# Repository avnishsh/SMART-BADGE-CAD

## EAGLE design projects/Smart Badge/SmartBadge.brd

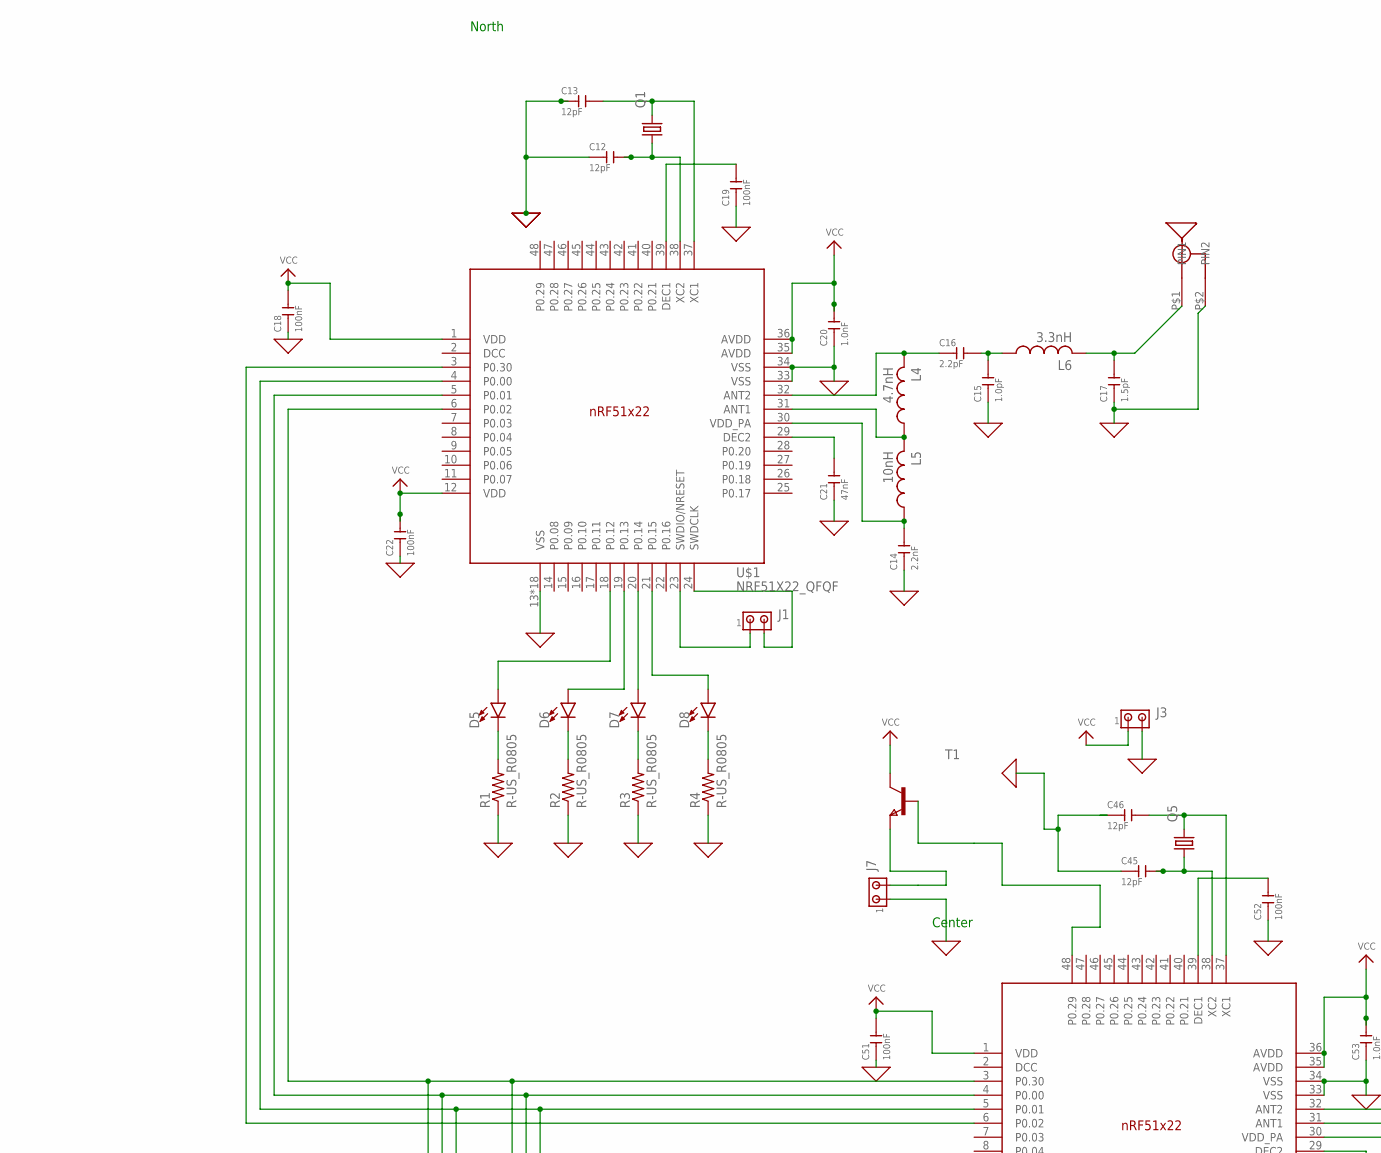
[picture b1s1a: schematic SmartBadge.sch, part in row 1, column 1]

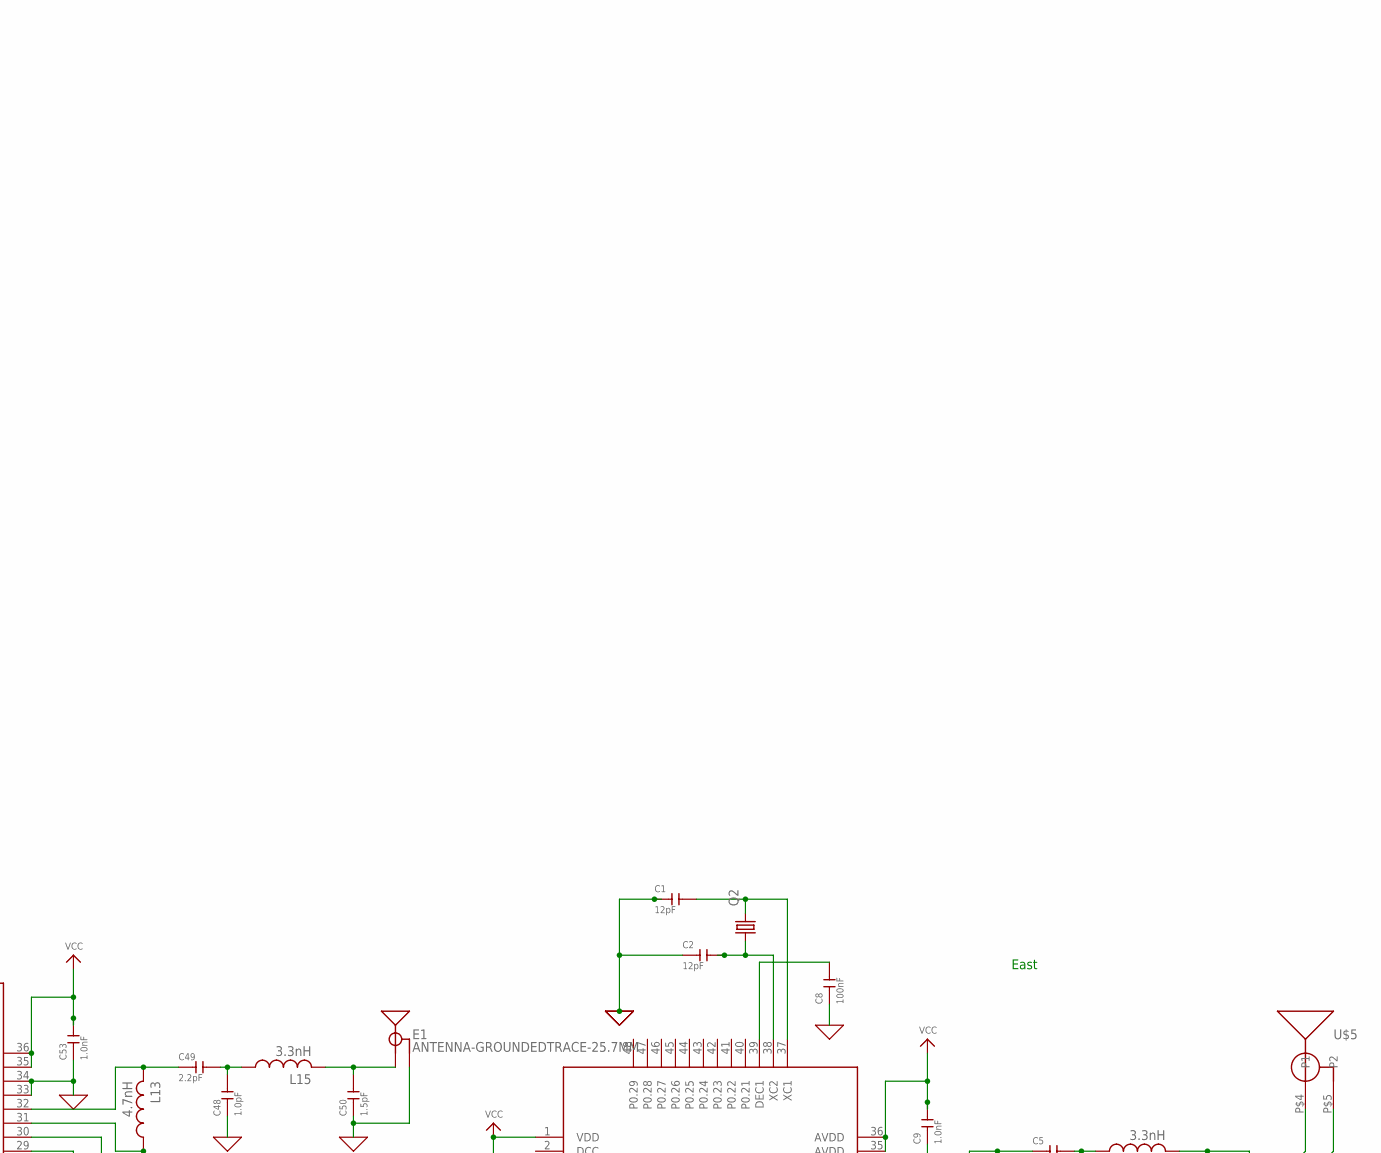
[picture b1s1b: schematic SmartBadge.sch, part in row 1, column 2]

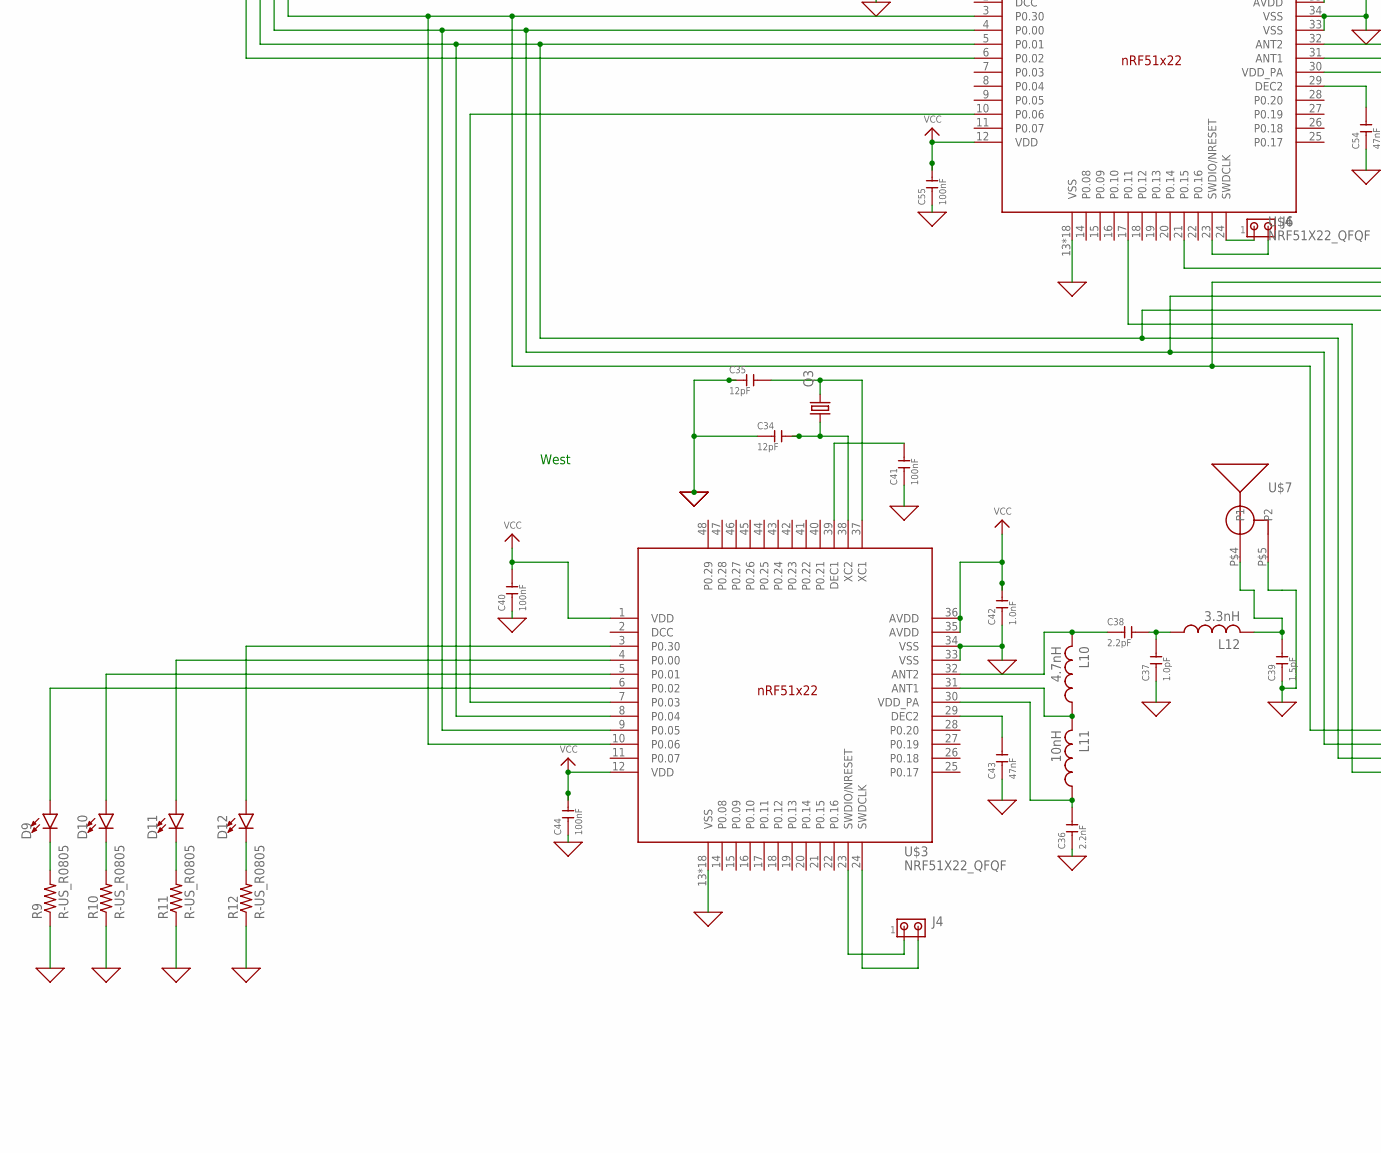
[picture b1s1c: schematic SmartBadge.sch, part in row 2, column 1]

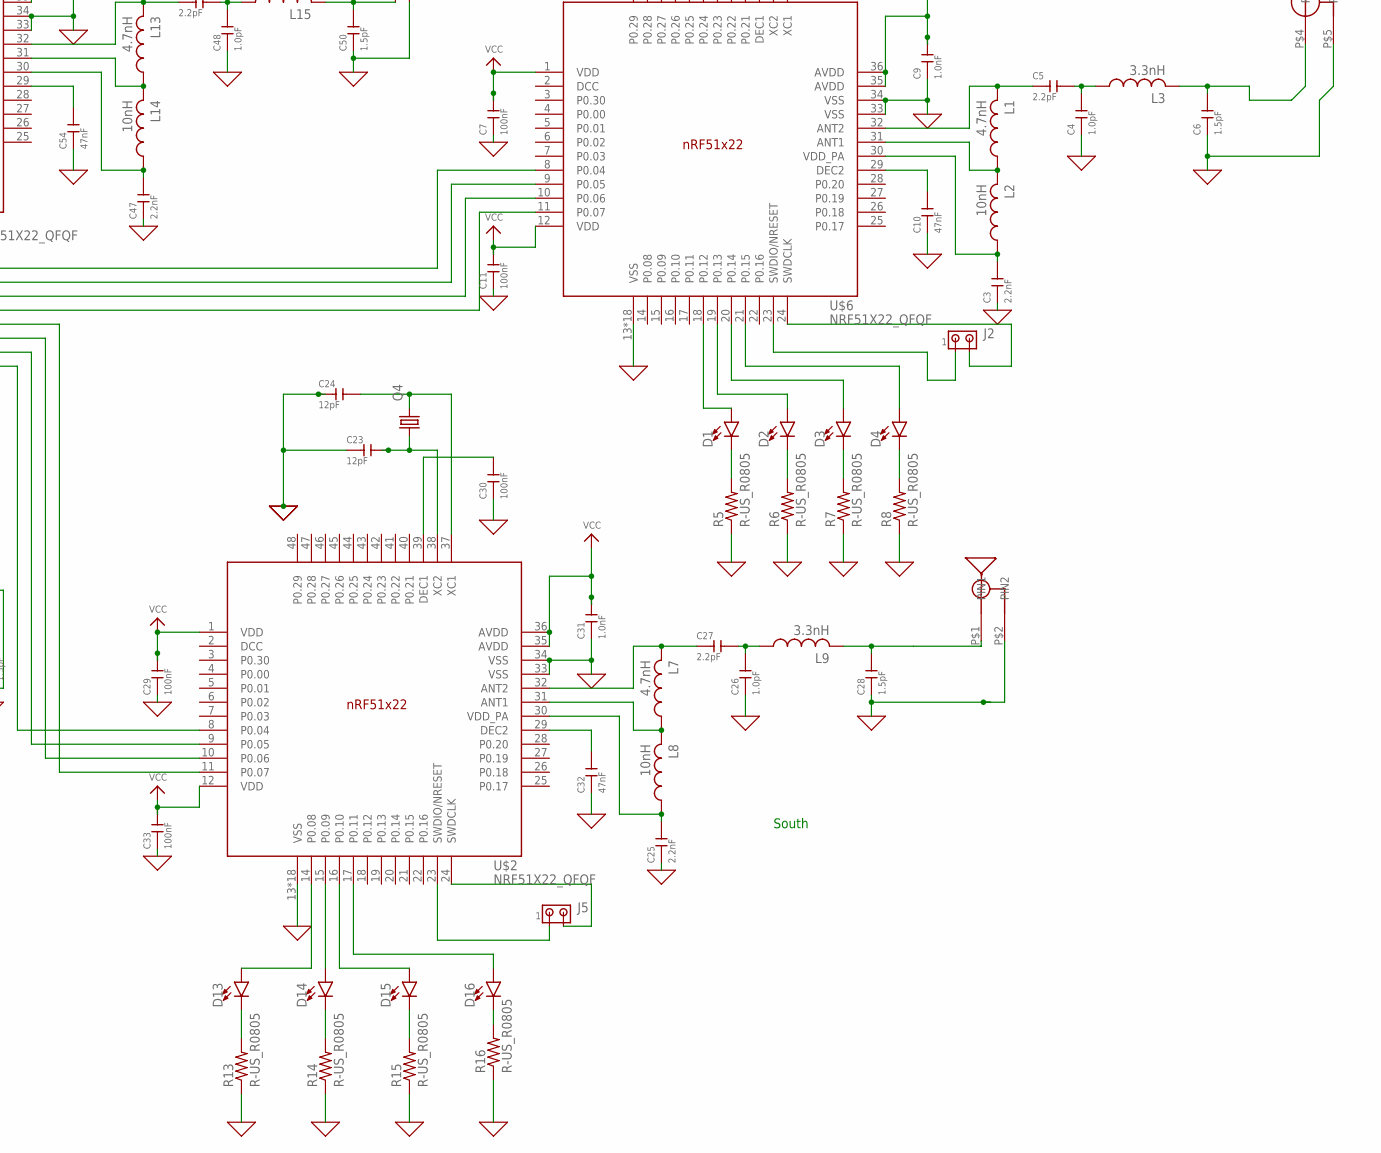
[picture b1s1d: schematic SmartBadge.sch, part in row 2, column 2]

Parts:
C1, C2, C12, C13, C23, C24, C34, C35, C45, C46: 12pF; C0805
C3, C14, C25, C36, C47: 2.2nF; C0805
C4, C15, C26, C37, C48: 1.0pF; C0805
C5, C16, C27, C38, C49: 2.2pF; C0805
C6, C17, C28, C39, C50: 1.5pF; C0805
C7, C8, C11, C18, C19, C22, C29, C30, C33, C40, C41, C44, C51, C52, C55: 100nF; C0805
C9, C20, C31, C42, C53: 1.0nF; C0805
C10, C21, C32, C43, C54: 47nF; C0805
D1, D2, D3, D4, D5, D6, D7, D8, D9, D10, D11, D12, D13, D14, D15, D16: LED-GREEN0603; LED-0603
E1: ANTENNA-GROUNDEDTRACE-25.7MM; TRACE_ANTENNA_2.4GHZ_25.7MM
J1, J2, J3, J4, J5, J6, J7: MTA02-100; 10X02MTA
L1, L4, L7, L10, L13: 4.7nH; RESC0805_L
L2, L5, L8, L11, L14: 10nH; RESC0805_L
L3, L6, L9, L12, L15: 3.3nH; RESC0805_L
Q1, Q2, Q3, Q4, Q5: KX-6; 2.5X2.0_KX-6
R1, R2, R3, R4, R5, R6, R7, R8, R9, R10, R11, R12, R13, R14, R15, R16: R-US_R0805; R0805
T1: NPNSOT323; SOT323
U$1, U$2, U$3, U$4, U$6: NRF51X22_QFQF; QFN40P600X600X90-48_N
U$5, U$7: YAGI_UDA; YAGIUDA
U$8, U$9: 2.4G_PATCH; PATCH

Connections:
0: C1.1, C2.1, C3.1, C4.1, C6.1, C7.1, C8.1, C9.1, C10.1, C11.1, C12.1, C13.1, C14.1, C15.1, C17.1, C18.1, C19.1, C20.1, C21.1, C22.1, C23.1, C24.1, C25.1, C26.1, C28.1, C29.1, C30.1, C31.1, C32.1, C33.1, C34.1, C35.1, C36.1, C37.1, C39.1, C40.1, C41.1, C42.1, C43.1, C44.1, C45.1, C46.1, C47.1, C48.1, C50.1, C51.1, C52.1, C53.1, C54.1, C55.1, E1.GND, E1.GND2 (GND), J3.2, J7.1, R1.1, R2.1, R3.1, R4.1, R5.1, R6.1, R7.1, R8.1, R9.1, R10.1, R11.1, R12.1, R13.1, R14.1, R15.1, R16.1, U$1.13 (VSS), U$1.33 (VSS), U$1.34 (VSS), U$1.PAD (VSS), U$1.PAD@VIA01 (VSS), U$1.PAD@VIA02 (VSS), U$1.PAD@VIA03 (VSS), U$1.PAD@VIA04 (VSS), U$1.PAD@VIA05 (VSS), U$1.PAD@VIA06 (VSS), U$1.PAD@VIA07 (VSS), U$1.PAD@VIA08 (VSS), U$1.PAD@VIA09 (VSS), U$1.PAD@VIA10 (VSS), U$1.PAD@VIA11 (VSS), U$1.PAD@VIA12 (VSS), U$1.PAD@VIA13 (VSS), U$1.PAD@VIA14 (VSS), U$1.PAD@VIA15 (VSS), U$1.PAD@VIA16 (VSS), U$2.13 (VSS), U$2.33 (VSS), U$2.34 (VSS), U$2.PAD (VSS), U$2.PAD@VIA01 (VSS), U$2.PAD@VIA02 (VSS), U$2.PAD@VIA03 (VSS), U$2.PAD@VIA04 (VSS), U$2.PAD@VIA05 (VSS), U$2.PAD@VIA06 (VSS), U$2.PAD@VIA07 (VSS), U$2.PAD@VIA08 (VSS), U$2.PAD@VIA09 (VSS), U$2.PAD@VIA10 (VSS), U$2.PAD@VIA11 (VSS), U$2.PAD@VIA12 (VSS), U$2.PAD@VIA13 (VSS), U$2.PAD@VIA14 (VSS), U$2.PAD@VIA15 (VSS), U$2.PAD@VIA16 (VSS), U$3.13 (VSS), U$3.33 (VSS), U$3.34 (VSS), U$3.PAD (VSS), U$3.PAD@VIA01 (VSS), U$3.PAD@VIA02 (VSS), U$3.PAD@VIA03 (VSS), U$3.PAD@VIA04 (VSS), U$3.PAD@VIA05 (VSS), U$3.PAD@VIA06 (VSS), U$3.PAD@VIA07 (VSS), U$3.PAD@VIA08 (VSS), U$3.PAD@VIA09 (VSS), U$3.PAD@VIA10 (VSS), U$3.PAD@VIA11 (VSS), U$3.PAD@VIA12 (VSS), U$3.PAD@VIA13 (VSS), U$3.PAD@VIA14 (VSS), U$3.PAD@VIA15 (VSS), U$3.PAD@VIA16 (VSS), U$4.13 (VSS), U$4.33 (VSS), U$4.34 (VSS), U$4.PAD (VSS), U$4.PAD@VIA01 (VSS), U$4.PAD@VIA02 (VSS), U$4.PAD@VIA03 (VSS), U$4.PAD@VIA04 (VSS), U$4.PAD@VIA05 (VSS), U$4.PAD@VIA06 (VSS), U$4.PAD@VIA07 (VSS), U$4.PAD@VIA08 (VSS), U$4.PAD@VIA09 (VSS), U$4.PAD@VIA10 (VSS), U$4.PAD@VIA11 (VSS), U$4.PAD@VIA12 (VSS), U$4.PAD@VIA13 (VSS), U$4.PAD@VIA14 (VSS), U$4.PAD@VIA15 (VSS), U$4.PAD@VIA16 (VSS), U$5.P$5 (P2), U$6.13 (VSS), U$6.33 (VSS), U$6.34 (VSS), U$6.PAD (VSS), U$6.PAD@VIA01 (VSS), U$6.PAD@VIA02 (VSS), U$6.PAD@VIA03 (VSS), U$6.PAD@VIA04 (VSS), U$6.PAD@VIA05 (VSS), U$6.PAD@VIA06 (VSS), U$6.PAD@VIA07 (VSS), U$6.PAD@VIA08 (VSS), U$6.PAD@VIA09 (VSS), U$6.PAD@VIA10 (VSS), U$6.PAD@VIA11 (VSS), U$6.PAD@VIA12 (VSS), U$6.PAD@VIA13 (VSS), U$6.PAD@VIA14 (VSS), U$6.PAD@VIA15 (VSS), U$6.PAD@VIA16 (VSS), U$7.P$5 (P2), U$8.P$2 (PIN2), U$9.P$2 (PIN2)
DCC: U$1.2 (DCC), U$2.2 (DCC), U$3.2 (DCC), U$4.2 (DCC), U$6.2 (DCC)
MISO: U$1.4 (P0.00), U$2.10 (P0.06), U$3.8 (P0.04), U$4.5 (P0.01), U$6.11 (P0.07)
MOSI: U$1.5 (P0.01), U$2.9 (P0.05), U$3.9 (P0.05), U$4.4 (P0.00), U$6.10 (P0.06)
unnamed: C8.2, U$6.39 (DEC1)
unnamed: C1.2, Q2.3 (2), U$6.37 (XC1)
unnamed: C10.2, U$6.29 (DEC2)
unnamed: C2.2, Q2.1, U$6.38 (XC2)
unnamed: C5.1, L1.2, U$6.32 (ANT2)
unnamed: L1.1, L2.2, U$6.31 (ANT1)
unnamed: C3.2, L2.1, U$6.30 (VDD_PA)
unnamed: C4.2, C5.2, L3.1
unnamed: C6.2, L3.2, U$5.P$4 (P1)
unnamed: C13.2, Q1.3 (2), U$1.37 (XC1)
unnamed: C12.2, Q1.1, U$1.38 (XC2)
unnamed: C19.2, U$1.39 (DEC1)
unnamed: C21.2, U$1.29 (DEC2)
unnamed: C16.1, L4.2, U$1.32 (ANT2)
unnamed: L4.1, L5.2, U$1.31 (ANT1)
unnamed: C14.2, L5.1, U$1.30 (VDD_PA)
unnamed: C15.2, C16.2, L6.1
unnamed: C17.2, L6.2, U$8.P$1 (PIN1)
unnamed: C24.2, Q4.3 (2), U$2.37 (XC1)
unnamed: C23.2, Q4.1, U$2.38 (XC2)
unnamed: C30.2, U$2.39 (DEC1)
unnamed: C32.2, U$2.29 (DEC2)
unnamed: C27.1, L7.2, U$2.32 (ANT2)
unnamed: L7.1, L8.2, U$2.31 (ANT1)
unnamed: C25.2, L8.1, U$2.30 (VDD_PA)
unnamed: C26.2, C27.2, L9.1
unnamed: C28.2, L9.2, U$9.P$1 (PIN1)
unnamed: C35.2, Q3.3 (2), U$3.37 (XC1)
unnamed: C34.2, Q3.1, U$3.38 (XC2)
unnamed: C41.2, U$3.39 (DEC1)
unnamed: C43.2, U$3.29 (DEC2)
unnamed: C38.1, L10.2, U$3.32 (ANT2)
unnamed: L10.1, L11.2, U$3.31 (ANT1)
unnamed: C36.2, L11.1, U$3.30 (VDD_PA)
unnamed: C37.2, C38.2, L12.1
unnamed: C39.2, L12.2, U$7.P$4 (P1)
unnamed: C46.2, Q5.3 (2), U$4.37 (XC1)
unnamed: C45.2, Q5.1, U$4.38 (XC2)
unnamed: C52.2, U$4.39 (DEC1)
unnamed: C54.2, U$4.29 (DEC2)
unnamed: C49.1, L13.2, U$4.32 (ANT2)
unnamed: L13.1, L14.2, U$4.31 (ANT1)
unnamed: C47.2, L14.1, U$4.30 (VDD_PA)
unnamed: C48.2, C49.2, L15.1
unnamed: C50.2, E1.ANT (SIGNAL), L15.2
unnamed: U$1.3 (P0.30), U$4.6 (P0.02)
unnamed: J6.2, U$4.23 (SWDIO/NRESET)
unnamed: T1.2 (B), U$4.48 (P0.29)
unnamed: J7.2, T1.3 (E)
unnamed: U$3.7 (P0.03), U$4.10 (P0.06)
unnamed: U$2.11 (P0.07), U$4.17 (P0.11)
unnamed: D1.A, U$6.18 (P0.12)
unnamed: D2.A, U$6.19 (P0.13)
unnamed: D3.A, U$6.20 (P0.14)
unnamed: D4.A, U$6.21 (P0.15)
unnamed: D5.A, U$1.18 (P0.12)
unnamed: D6.A, U$1.19 (P0.13)
unnamed: D7.A, U$1.20 (P0.14)
unnamed: D8.A, U$1.21 (P0.15)
unnamed: D12.A, U$3.3 (P0.30)
unnamed: D11.A, U$3.4 (P0.00)
unnamed: D10.A, U$3.5 (P0.01)
unnamed: D9.A, U$3.6 (P0.02)
unnamed: D13.A, U$2.14 (P0.08)
unnamed: D14.A, U$2.15 (P0.09)
unnamed: D15.A, U$2.16 (P0.10)
unnamed: D16.A, U$2.17 (P0.11)
unnamed: D5.C, R1.2
unnamed: D6.C, R2.2
unnamed: D7.C, R3.2
unnamed: D8.C, R4.2
unnamed: D1.C, R5.2
unnamed: D2.C, R6.2
unnamed: D3.C, R7.2
unnamed: D4.C, R8.2
unnamed: D13.C, R13.2
unnamed: D14.C, R14.2
unnamed: D15.C, R15.2
unnamed: D16.C, R16.2
unnamed: D12.C, R12.2
unnamed: D11.C, R11.2
unnamed: D10.C, R10.2
unnamed: D9.C, R9.2
unnamed: U$4.21 (P0.15), U$6.8 (P0.04)
unnamed: J4.1, U$3.23 (SWDIO/NRESET)
unnamed: J4.2, U$3.24 (SWDCLK)
unnamed: J5.1, U$2.23 (SWDIO/NRESET)
unnamed: J5.2, U$2.24 (SWDCLK)
unnamed: J2.1, U$6.23 (SWDIO/NRESET)
unnamed: J2.2, U$6.24 (SWDCLK)
unnamed: J1.1, U$1.23 (SWDIO/NRESET)
unnamed: J1.2, U$1.24 (SWDCLK)
unnamed: J6.1, U$4.24 (SWDCLK)
SCK: U$1.6 (P0.02), U$2.8 (P0.04), U$3.10 (P0.06), U$4.3 (P0.30), U$6.9 (P0.05)
VCC: C7.2, C9.2, C11.2, C18.2, C20.2, C22.2, C29.2, C31.2, C33.2, C40.2, C42.2, C44.2, C51.2, C53.2, C55.2, J3.1, T1.1 (C), U$1.1 (VDD), U$1.12 (VDD), U$1.35 (AVDD), U$1.36 (AVDD), U$2.1 (VDD), U$2.12 (VDD), U$2.35 (AVDD), U$2.36 (AVDD), U$3.1 (VDD), U$3.12 (VDD), U$3.35 (AVDD), U$3.36 (AVDD), U$4.1 (VDD), U$4.12 (VDD), U$4.35 (AVDD), U$4.36 (AVDD), U$6.1 (VDD), U$6.12 (VDD), U$6.35 (AVDD), U$6.36 (AVDD)

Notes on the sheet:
North
South
East
West
Center

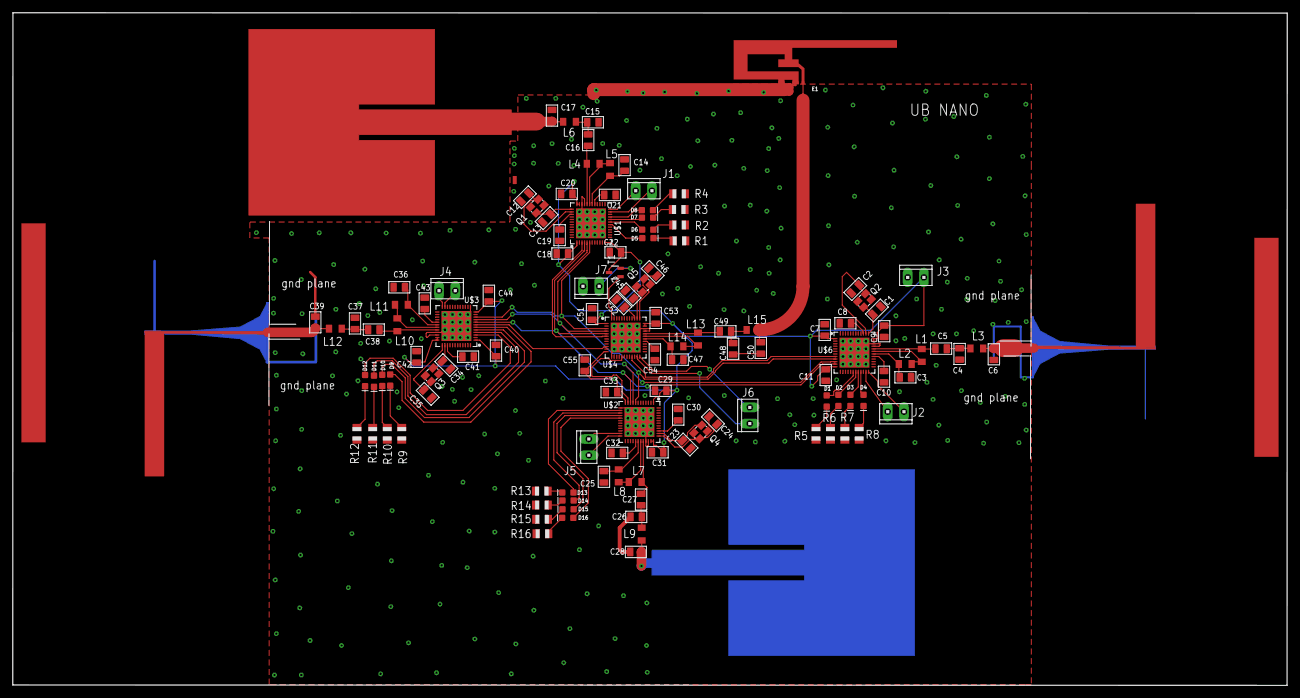
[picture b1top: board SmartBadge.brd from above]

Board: 2 copper layers, 199.5 x 105.3 mm, 125 parts (1 on the bottom side), 99 nets.

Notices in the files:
parts and their libraries:
crystal-geyer_V1_0: Copyright: Geyer-Electronic
SparkFun-LED: Licensing: Creative Commons ShareAlike 4.0 International - https://creativecommons.org/licenses/by-sa/4.0
